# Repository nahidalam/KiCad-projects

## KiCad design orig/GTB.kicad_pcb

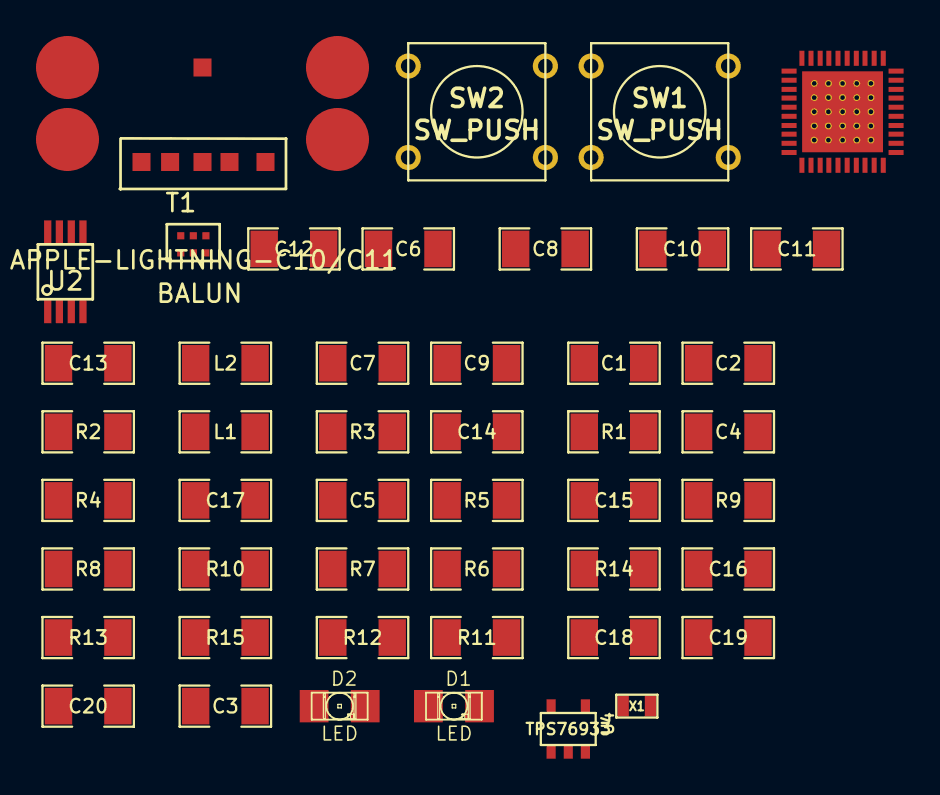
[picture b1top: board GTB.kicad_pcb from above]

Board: 2 copper layers, 47 parts (0 on the bottom side), 33 nets, no tracks yet.

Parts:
C1: 10P; SM1206
C2, C7, C18: 1U; SM1206
C3, C5, C6, C8, C11: 100N; SM1206
C4: 1N; SM1206
C9, C12: 27P; SM1206
C10: 220P; SM1206
C13: 2U; SM1206
C14, C16, C17, C19: C; SM1206
C15: 0.1U; SM1206
C20: 4U7; SM1206
D1, D2: LED; LED-1206
L1: 6N8; SM1206
L2: INDUCTOR; SM1206
R1: 2K2; SM1206
R2: 56K; SM1206
R3, R10, R13: 0; SM1206
R4, R5: 2.2K; SM1206
R6, R7: 33; SM1206
R8, R15: R; SM1206
R9: 1K5; SM1206
R11, R12: 270; SM1206
R14: 2; SM1206
SW1, SW2: SW_PUSH; SW_PUSH_SMALL
T1: BALUN; JTI_2450BM15A0002
U1: CC2531; RHA40_4P5X4P5
U2: APPLE-CP; SSOP8
U3: APPLE-LIGHTNING-C10/C11; Lightning-C11-B
U4: TPS76933; SOT23-5
X1: CRYSTAL; SM0603

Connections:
3V3: L2.1, R8.1, R13.1, R15.2
GND: C1.2, C2.2, C3.2, C4.2, C5.2, C6.2, C7.2, C8.2, C9.2, C10.2, C11.2, C12.2, C13.2, C14.2, C15.2, C16.2, C17.2, C18.2, C19.2, D1.2, R2.2, R3.1, R14.2, SW1.1, SW2.1, T1.3, T1.5, T1.6, U1.1, U2.1, U2.7, U3.1, U3.9, U4.2, U4.3
unnamed: T1.2, U1.26
unnamed: T1.1, U1.25
unnamed: L1.1, R2.1
unnamed: L1.2, U1.30
unnamed: C7.1, U1.40
unnamed: C9.1, X1.1
unnamed: C14.1, R3.2, T1.4
unnamed: C12.1, U1.22, X1.2
unnamed: C2.1, U1.39
unnamed: C4.1, R1.1, U1.20
unnamed: C3.1, U1.10
unnamed: C20.2, R14.1
unnamed: C19.1, U4.4
unnamed: C20.1, R13.2, U4.5
unnamed: R8.2, R9.1, R10.2
unnamed: D1.1, R11.2
unnamed: D2.1, R12.2
unnamed: R5.1, U2.6
unnamed: C15.1, U2.8
unnamed: R4.1, U2.2
unnamed: C17.1, R7.1, U3.3
unnamed: C16.1, R6.1, R9.2, U3.2
P0_0: D2.2, U1.19
P1_0/LED: R10.1, U1.11
P1_2: SW1.2, U1.8
P1_3: SW2.2, U1.7
PA_DM: R7.2, U1.3
PA_DP: R6.2, U1.2
VBUS: C18.1, U3.5, U4.1
VCC: C1.1, C5.1, C6.1, C8.1, C10.1, C11.1, C13.1, L2.2, R4.2, R5.2, U1.4, U1.21, U1.24, U1.27, U1.28, U1.29, U1.31
VCC_EXT: R15.1, U3.4

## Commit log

2014-05-14 init commit
